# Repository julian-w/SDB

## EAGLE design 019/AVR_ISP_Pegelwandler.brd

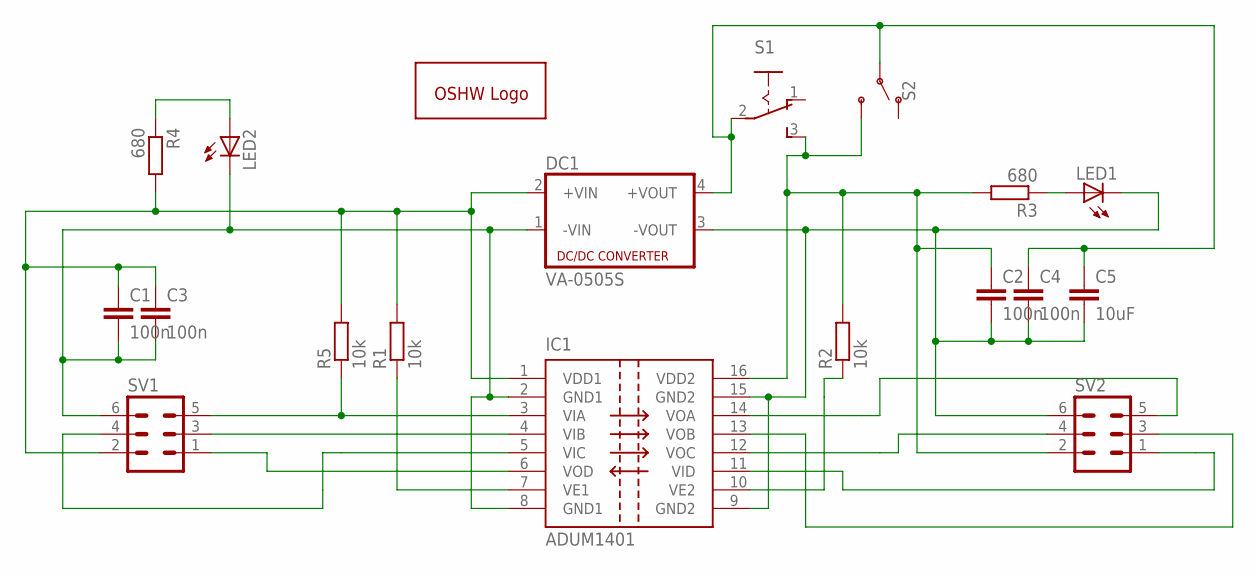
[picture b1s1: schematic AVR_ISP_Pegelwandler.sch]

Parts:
C1, C2, C3, C4: 100n; C1206
C5: 10uF; C1206
DC1: VA-0505S; 4SIL
GOLD_ORB_SM1: OSHWLOGOLOGO5MM; OSHW_5MM
IC1: ADUM1401; SO16W
LED1, LED2: LEDCHIPLED_1206; CHIPLED_1206
R1, R2, R5: 10k; R1206
R3, R4: 680; R1206
S1: 255SB
S2: SWITCH-SPDT-PTH-11.6X4.0MM; SWITCH_SPDT_PTH_11.6X4.0MM
SV1, SV2: ML6

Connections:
GND1@2: C1.2, C3.2, DC1.1 (-VIN), IC1.2 (GND1), IC1.8 (GND1), LED2.C, SV1.6
GND2@2: C2.2, C4.2, C5.2, DC1.3 (-VOUT), IC1.9 (GND2), IC1.15 (GND2), LED1.C, SV2.6
unnamed: C1.1, C3.1, DC1.2 (+VIN), IC1.1 (VDD1), R1.2, R4.2, R5.2, SV1.2
unnamed: C2.1, IC1.16 (VDD2), R2.2, R3.2, S1.3 (S), S2.3 (S), SV2.2
unnamed: LED1.A, R3.1
unnamed: IC1.4 (VIB), SV1.3
unnamed: IC1.13 (VOB), SV2.3
unnamed: IC1.14 (VOA), SV2.5
unnamed: IC1.11 (VID), SV2.1
unnamed: IC1.6 (VOD), SV1.1
unnamed: IC1.12 (VOC), SV2.4
unnamed: IC1.5 (VIC), SV1.4
unnamed: IC1.3 (VIA), R5.1, SV1.5
unnamed: IC1.7 (VE1), R1.1
unnamed: IC1.10 (VE2), R2.1
unnamed: C4.1, C5.1, DC1.4 (+VOUT), S1.2, S2.2
unnamed: LED2.A, R4.1

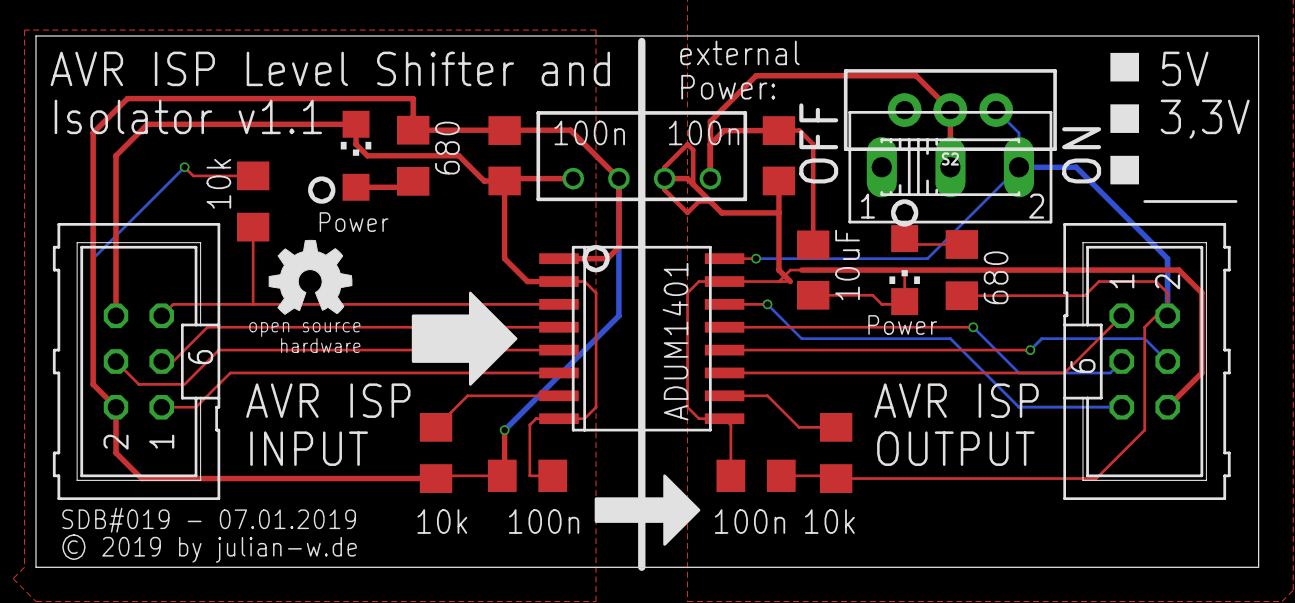
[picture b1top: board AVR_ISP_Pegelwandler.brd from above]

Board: 2 copper layers, 67.9 x 29.5 mm, 19 parts (0 on the bottom side), 17 nets.

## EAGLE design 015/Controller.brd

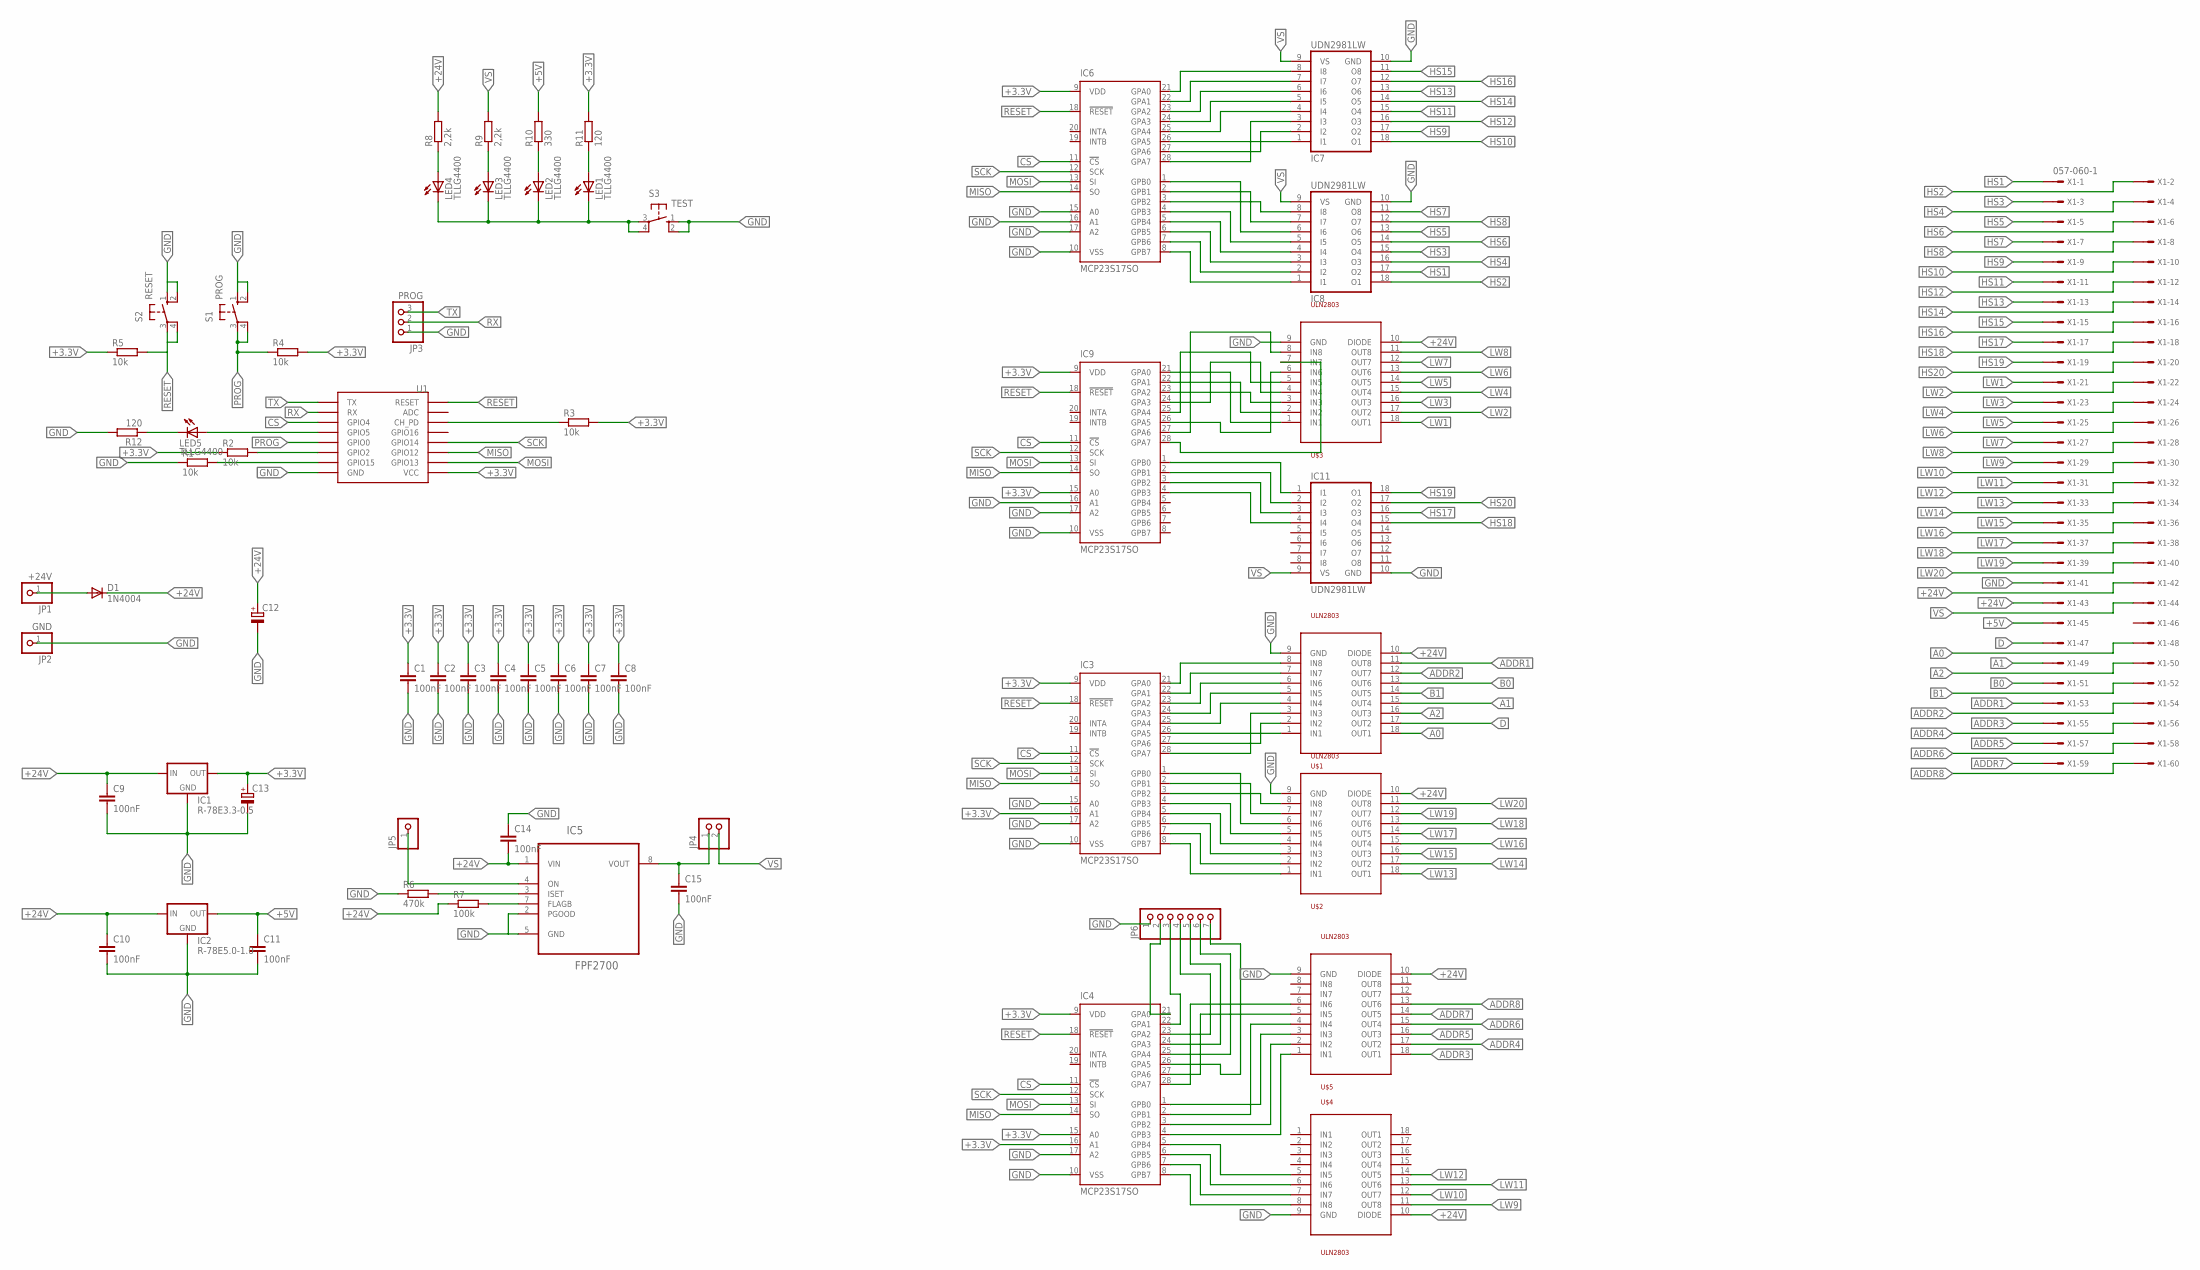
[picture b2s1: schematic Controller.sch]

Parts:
C1, C2, C3, C4, C5, C6, C7, C8, C9, C10, C11, C14, C15: 100nF; C1206
C12, C13: CPOL-EUE2.5-5; E2,5-5
D1: 1N4004; DO41-10
IC1: R-78E3.3-0.5; SIP3
IC2: R-78E5.0-1.0; SIP3
IC3, IC4, IC6, IC9: MCP23S17SO; SO28W
IC5: FPF2700; SOIC127P600X175-8N
IC7, IC8, IC11: UDN2981LW; SO18W
JP1: +24V; 1X01
JP2: GND; 1X01
JP3: PROG; 1X03
JP4: PINHD-1X2; 1X02
JP5: PINHD-1X1; 1X01
JP6: PINHD-1X7; 1X07
LED1, LED2, LED3, LED4, LED5: TLLG4400; LED3MM
R1, R2, R3, R4, R5: 10k; R1206
R6: 470k; 0207/10
R7: 100k; 0207/10
R8, R9: 2,2k; R1206
R10: 330; R1206
R11, R12: 120; R1206
S1: PROG; B3F-10XX
S2: RESET; B3F-10XX
S3: TEST; B3F-10XX
U1: ESP12SMD; ESP12-SMD
U$1, U$2, U$3, U$4, U$5: ULN2803; SO18L
X1: 057-060-1

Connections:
+3.3V: C1.1, C2.1, C3.1, C4.1, C5.1, C6.1, C7.1, C8.1, C13.+, IC1.3 (OUT), IC3.9 (VDD), IC3.16 (A1), IC4.9 (VDD), IC4.15 (A0), IC4.16 (A1), IC6.9 (VDD), IC9.9 (VDD), IC9.15 (A0), R2.1, R3.2, R4.2, R5.1, R11.2, U1.VCC
+5V: C11.1, IC2.3 (OUT), R10.2, X1.45
+24V: C9.1, C10.1, C12.+, C14.2, D1.C, IC1.1 (IN), IC2.1 (IN), IC5.1 (VIN), R7.1, R8.2, U$1.10 (DIODE), U$2.10 (DIODE), U$3.10 (DIODE), U$4.10 (DIODE), U$5.10 (DIODE), X1.42, X1.43
A0: U$1.18 (OUT1), X1.48
A1: U$1.15 (OUT4), X1.49
A2: U$1.16 (OUT3), X1.50
ADDR1: U$1.11 (OUT8), X1.53
ADDR2: U$1.12 (OUT7), X1.54
ADDR3: U$5.18 (OUT1), X1.55
ADDR4: U$5.17 (OUT2), X1.56
ADDR5: U$5.16 (OUT3), X1.57
ADDR6: U$5.15 (OUT4), X1.58
ADDR7: U$5.14 (OUT5), X1.59
ADDR8: U$5.13 (OUT6), X1.60
B0: U$1.13 (OUT6), X1.51
B1: U$1.14 (OUT5), X1.52
CS: IC3.11 (!CS), IC4.11 (!CS), IC6.11 (!CS), IC9.11 (!CS), U1.GPIO4
D: U$1.17 (OUT2), X1.47
GND: C1.2, C2.2, C3.2, C4.2, C5.2, C6.2, C7.2, C8.2, C9.2, C10.2, C11.2, C12.-, C13.-, C14.1, C15.2, IC1.2 (GND), IC2.2 (GND), IC3.10 (VSS), IC3.15 (A0), IC3.17 (A2), IC4.10 (VSS), IC4.17 (A2), IC5.2 (PGOOD), IC5.5 (GND), IC6.10 (VSS), IC6.15 (A0), IC6.16 (A1), IC6.17 (A2), IC7.10 (GND), IC8.10 (GND), IC9.10 (VSS), IC9.16 (A1), IC9.17 (A2), IC11.10 (GND), JP2.1, JP3.1, JP6.1, R1.1, R6.1, R12.2, S1.1 (S), S1.2 (S1), S2.1 (S), S2.2 (S1), S3.1 (S), S3.2 (S1), U1.GND, U$1.9 (GND), U$2.9 (GND), U$3.9 (GND), U$4.9 (GND), U$5.9 (GND), X1.41
HS1: IC8.17 (O2), X1.1
HS2: IC8.18 (O1), X1.2
HS3: IC8.15 (O4), X1.3
HS4: IC8.16 (O3), X1.4
HS5: IC8.13 (O6), X1.5
HS6: IC8.14 (O5), X1.6
HS7: IC8.11 (O8), X1.7
HS8: IC8.12 (O7), X1.8
HS9: IC7.17 (O2), X1.9
HS10: IC7.18 (O1), X1.10
HS11: IC7.15 (O4), X1.11
HS12: IC7.16 (O3), X1.12
HS13: IC7.13 (O6), X1.13
HS14: IC7.14 (O5), X1.14
HS15: IC7.11 (O8), X1.15
HS16: IC7.12 (O7), X1.16
HS17: IC11.16 (O3), X1.17
HS18: IC11.15 (O4), X1.18
HS19: IC11.18 (O1), X1.19
HS20: IC11.17 (O2), X1.20
LW1: U$3.18 (OUT1), X1.21
LW2: U$3.17 (OUT2), X1.22
LW3: U$3.16 (OUT3), X1.23
LW4: U$3.15 (OUT4), X1.24
LW5: U$3.14 (OUT5), X1.25
LW6: U$3.13 (OUT6), X1.26
LW7: U$3.12 (OUT7), X1.27
LW8: U$3.11 (OUT8), X1.28
LW9: U$4.11 (OUT8), X1.29
LW10: U$4.12 (OUT7), X1.30
LW11: U$4.13 (OUT6), X1.31
LW12: U$4.14 (OUT5), X1.32
LW13: U$2.18 (OUT1), X1.33
LW14: U$2.17 (OUT2), X1.34
LW15: U$2.16 (OUT3), X1.35
LW16: U$2.15 (OUT4), X1.36
LW17: U$2.14 (OUT5), X1.37
LW18: U$2.13 (OUT6), X1.38
LW19: U$2.12 (OUT7), X1.39
LW20: U$2.11 (OUT8), X1.40
MISO: IC3.14 (SO), IC4.14 (SO), IC6.14 (SO), IC9.14 (SO), U1.GPIO12
MOSI: IC3.13 (SI), IC4.13 (SI), IC6.13 (SI), IC9.13 (SI), U1.GPIO13
unnamed: R2.2, U1.GPIO2
unnamed: R1.2, U1.GPIO15
unnamed: IC3.21 (GPA0), U$1.8 (IN8)
unnamed: R3.1, U1.CH_PD
unnamed: C15.1, IC5.8 (VOUT), JP4.1
unnamed: IC5.3 (ISET), R6.2
unnamed: IC3.22 (GPA1), U$1.7 (IN7)
unnamed: IC3.23 (GPA2), U$1.6 (IN6)
unnamed: IC3.24 (GPA3), U$1.5 (IN5)
unnamed: IC3.25 (GPA4), U$1.4 (IN4)
unnamed: IC3.26 (GPA5), U$1.1 (IN1)
unnamed: IC3.27 (GPA6), U$1.2 (IN2)
unnamed: IC3.28 (GPA7), U$1.3 (IN3)
unnamed: IC3.3 (GPB2), U$2.8 (IN8)
unnamed: IC3.2 (GPB1), U$2.7 (IN7)
unnamed: IC3.1 (GPB0), U$2.6 (IN6)
unnamed: IC3.4 (GPB3), U$2.5 (IN5)
unnamed: IC3.5 (GPB4), U$2.4 (IN4)
unnamed: IC3.6 (GPB5), U$2.3 (IN3)
unnamed: IC3.7 (GPB6), U$2.2 (IN2)
unnamed: IC3.8 (GPB7), U$2.1 (IN1)
unnamed: IC4.28 (GPA7), U$5.6 (IN6)
unnamed: IC4.27 (GPA6), U$5.5 (IN5)
unnamed: IC4.4 (GPB3), U$5.1 (IN1)
unnamed: IC4.3 (GPB2), U$5.2 (IN2)
unnamed: IC4.2 (GPB1), U$5.4 (IN4)
unnamed: IC4.1 (GPB0), U$5.3 (IN3)
unnamed: D1.A, JP1.1
unnamed: IC5.7 (FLAGB), R7.2
unnamed: IC5.4 (ON), JP5.1
unnamed: LED1.K (C), LED2.K (C), LED3.K (C), LED4.K (C), S3.3, S3.4 (P1)
unnamed: LED4.A, R8.1
unnamed: LED3.A, R9.1
unnamed: IC4.5 (GPB4), U$4.5 (IN5)
unnamed: IC4.6 (GPB5), U$4.6 (IN6)
unnamed: IC4.7 (GPB6), U$4.7 (IN7)
unnamed: IC4.8 (GPB7), U$4.8 (IN8)
unnamed: IC6.21 (GPA0), IC7.8 (I8)
unnamed: IC6.22 (GPA1), IC7.7 (I7)
unnamed: IC6.23 (GPA2), IC7.6 (I6)
unnamed: IC6.24 (GPA3), IC7.5 (I5)
unnamed: IC6.25 (GPA4), IC7.4 (I4)
unnamed: IC6.4 (GPB3), IC8.5 (I5)
unnamed: IC6.5 (GPB4), IC8.4 (I4)
unnamed: IC6.6 (GPB5), IC8.3 (I3)
unnamed: IC6.7 (GPB6), IC8.2 (I2)
unnamed: IC6.8 (GPB7), IC8.1 (I1)
unnamed: IC6.26 (GPA5), IC7.1 (I1)
unnamed: IC6.27 (GPA6), IC7.2 (I2)
unnamed: IC6.28 (GPA7), IC7.3 (I3)
unnamed: IC6.3 (GPB2), IC8.8 (I8)
unnamed: IC6.2 (GPB1), IC8.7 (I7)
unnamed: IC6.1 (GPB0), IC8.6 (I6)
unnamed: IC9.21 (GPA0), U$3.1 (IN1)
unnamed: IC9.22 (GPA1), U$3.2 (IN2)
unnamed: IC9.23 (GPA2), U$3.3 (IN3)
unnamed: IC9.24 (GPA3), U$3.4 (IN4)
unnamed: IC9.25 (GPA4), U$3.5 (IN5)
unnamed: IC9.1 (GPB0), IC11.1 (I1)
unnamed: IC9.2 (GPB1), IC11.2 (I2)
unnamed: IC9.3 (GPB2), IC11.3 (I3)
unnamed: IC9.4 (GPB3), IC11.4 (I4)
unnamed: IC9.26 (GPA5), U$3.6 (IN6)
unnamed: IC9.27 (GPA6), U$3.8 (IN8)
unnamed: LED2.A, R10.1
unnamed: IC9.28 (GPA7), U$3.7 (IN7)
unnamed: LED1.A, R11.1
unnamed: IC4.21 (GPA0), JP6.2
unnamed: IC4.22 (GPA1), JP6.3
unnamed: IC4.23 (GPA2), JP6.4
unnamed: IC4.24 (GPA3), JP6.5
unnamed: IC4.25 (GPA4), JP6.6
unnamed: IC4.26 (GPA5), JP6.7
unnamed: LED5.A, U1.GPIO5
unnamed: LED5.K (C), R12.1
PROG: R4.1, S1.3, S1.4 (P1), U1.GPIO0
RESET: IC3.18 (!RESET), IC4.18 (!RESET), IC6.18 (!RESET), IC9.18 (!RESET), R5.2, S2.3, S2.4 (P1), U1.RESET
RX: JP3.2, U1.RXD0 (RX)
SCK: IC3.12 (SCK), IC4.12 (SCK), IC6.12 (SCK), IC9.12 (SCK), U1.GPIO14
TX: JP3.3, U1.TXD0 (TX)
VS: IC7.9 (VS), IC8.9 (VS), IC11.9 (VS), JP4.2, R9.2, X1.44

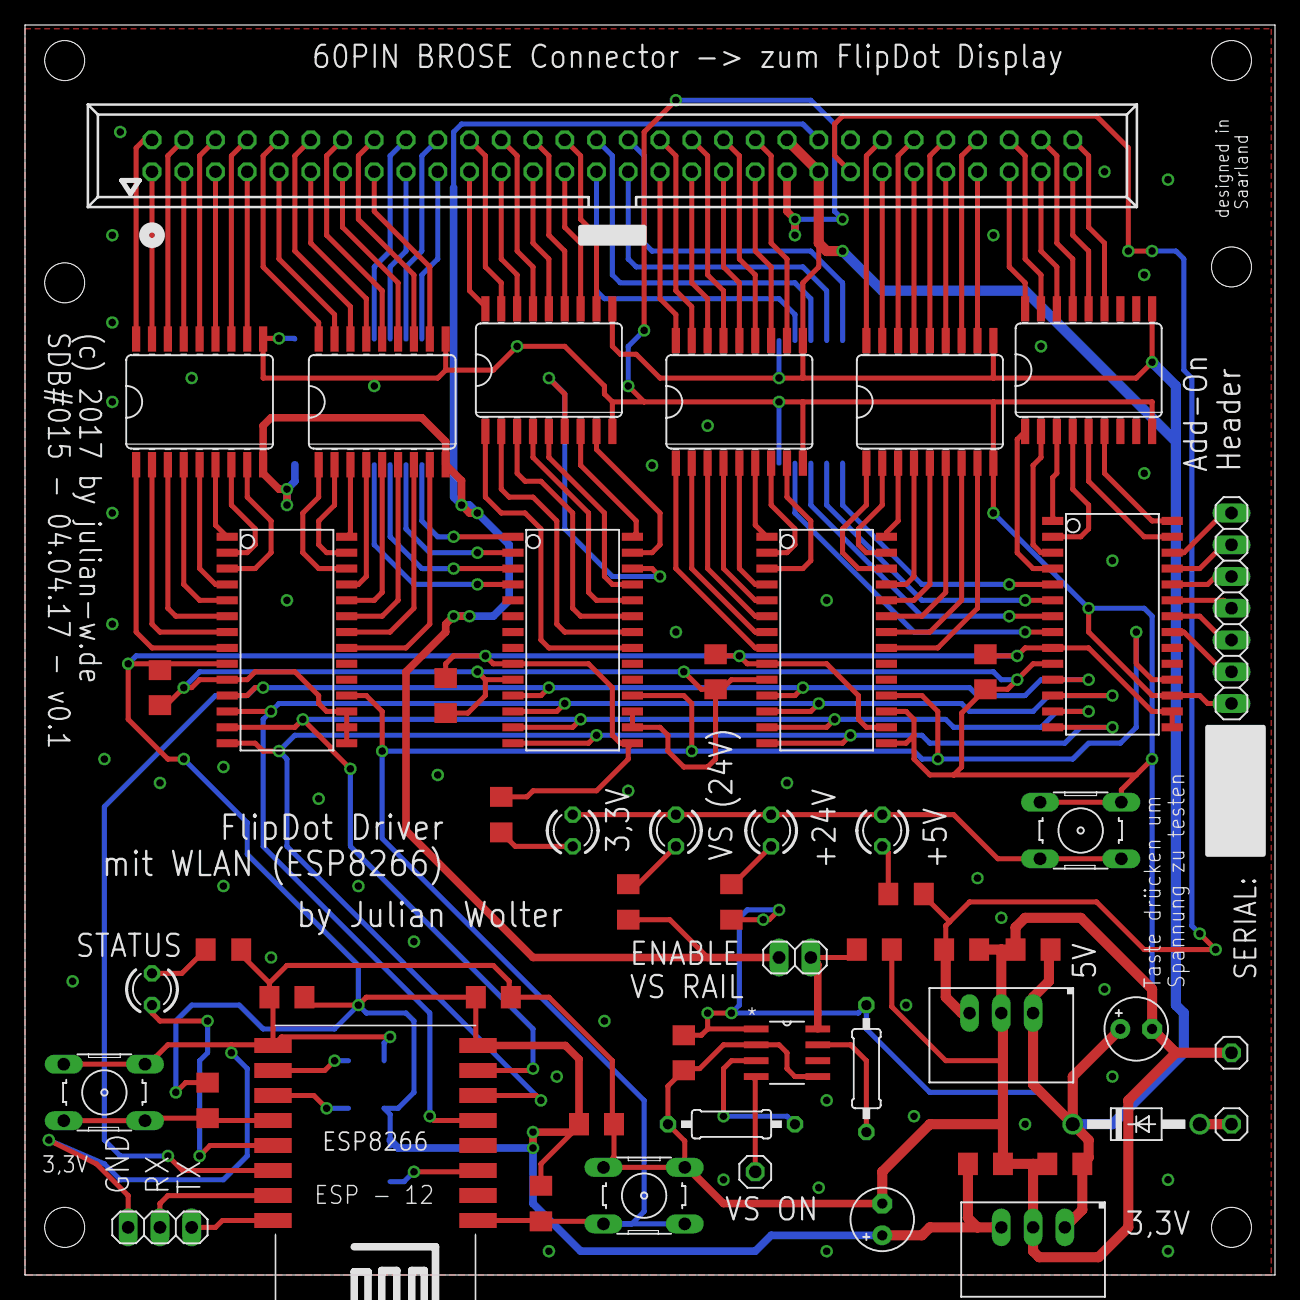
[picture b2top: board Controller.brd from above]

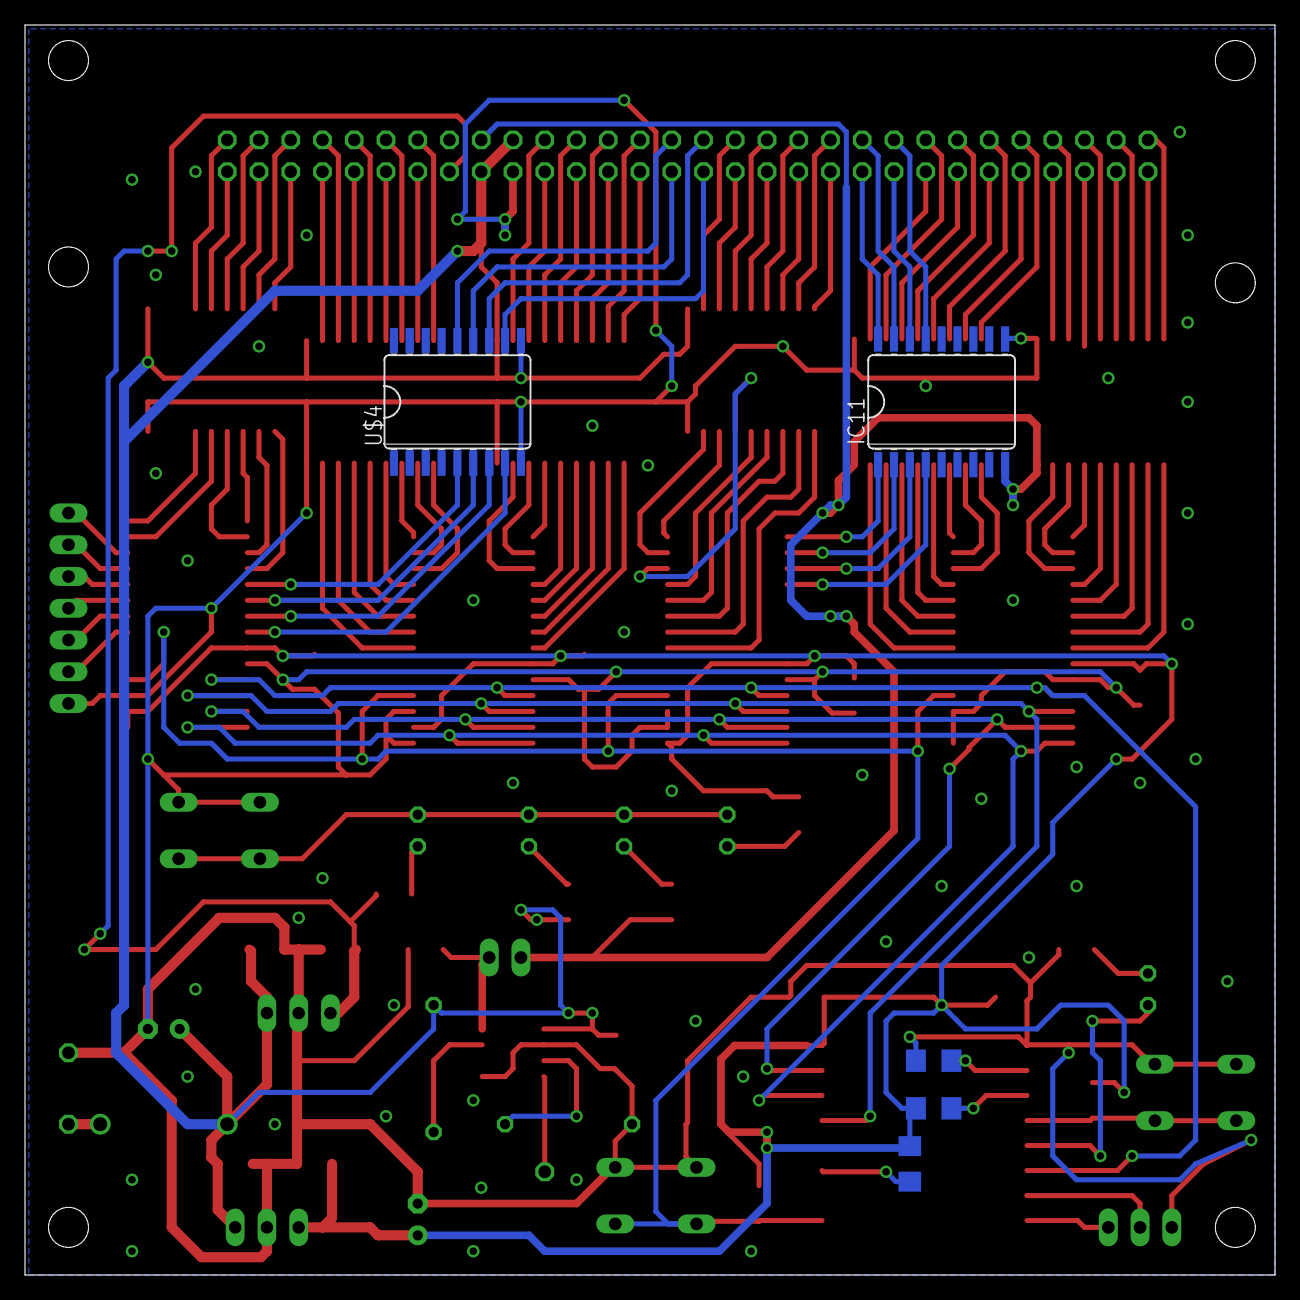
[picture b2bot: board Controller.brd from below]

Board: 2 copper layers, 100.0 x 100.0 mm, 59 parts (5 on the bottom side), 142 nets.

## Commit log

2021-04-18 inital push of data
2021-04-20 addin designs 025, 026 and 027
2021-04-25 adding SDB#028
2021-05-16 fixing wrong component in BOM
2021-06-22 adding SDB #29
2021-07-04 adding new boards to SDB (030, 031)
2021-07-23 updating partlist
2021-08-10 adding missing drill files
2022-11-01 updating SDB
2022-11-09 fixing naming SDA/SCL

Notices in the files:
015/Controller.brd:
(c) 2017 by julian-w.de
019/AVR_ISP_Pegelwandler.brd:
© 2019 by julian-w.de
parts and their libraries:
r-78xx_10: (c) 2015 Samuel Lourenço
SparkFun-Switches: Licensing: Creative Commons ShareAlike 4.0 International - https://creativecommons.org/licenses/by-sa/4.0
